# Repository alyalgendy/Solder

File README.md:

# 3-Bit Binary counter

## Schematic Design

## BCP Design
### Front

### Back

## 3D view

## Features

- Counts from 0 (000) to 7 (111) in binary, covering all 3-bit combinations.
- Three LEDs display the binary output, each representing one bit.
- Easily observe the counter state through the LED indicators.
- Optimized for a small, easy-to-assemble printed circuit board.
- Ideal for learning and demonstrating binary counting and digital electronics basics.
- Uses standard logic Transistors and LEDs for efficient operation.

## BOM
- 2  Battery holder
- 1  10μF Capacitor
- 3  LEDs
- 9  NPN transistors
- 1  Push Button
- 14 100 Ω Resistor
- 3  220 Ω Resistor
- 6  4.7 kΩ Resistor
- 4  47 kΩ Resistor

Made by `@Aly Al-gendy` on slack :D

Made as a part of http://solder.hackclub.com/!

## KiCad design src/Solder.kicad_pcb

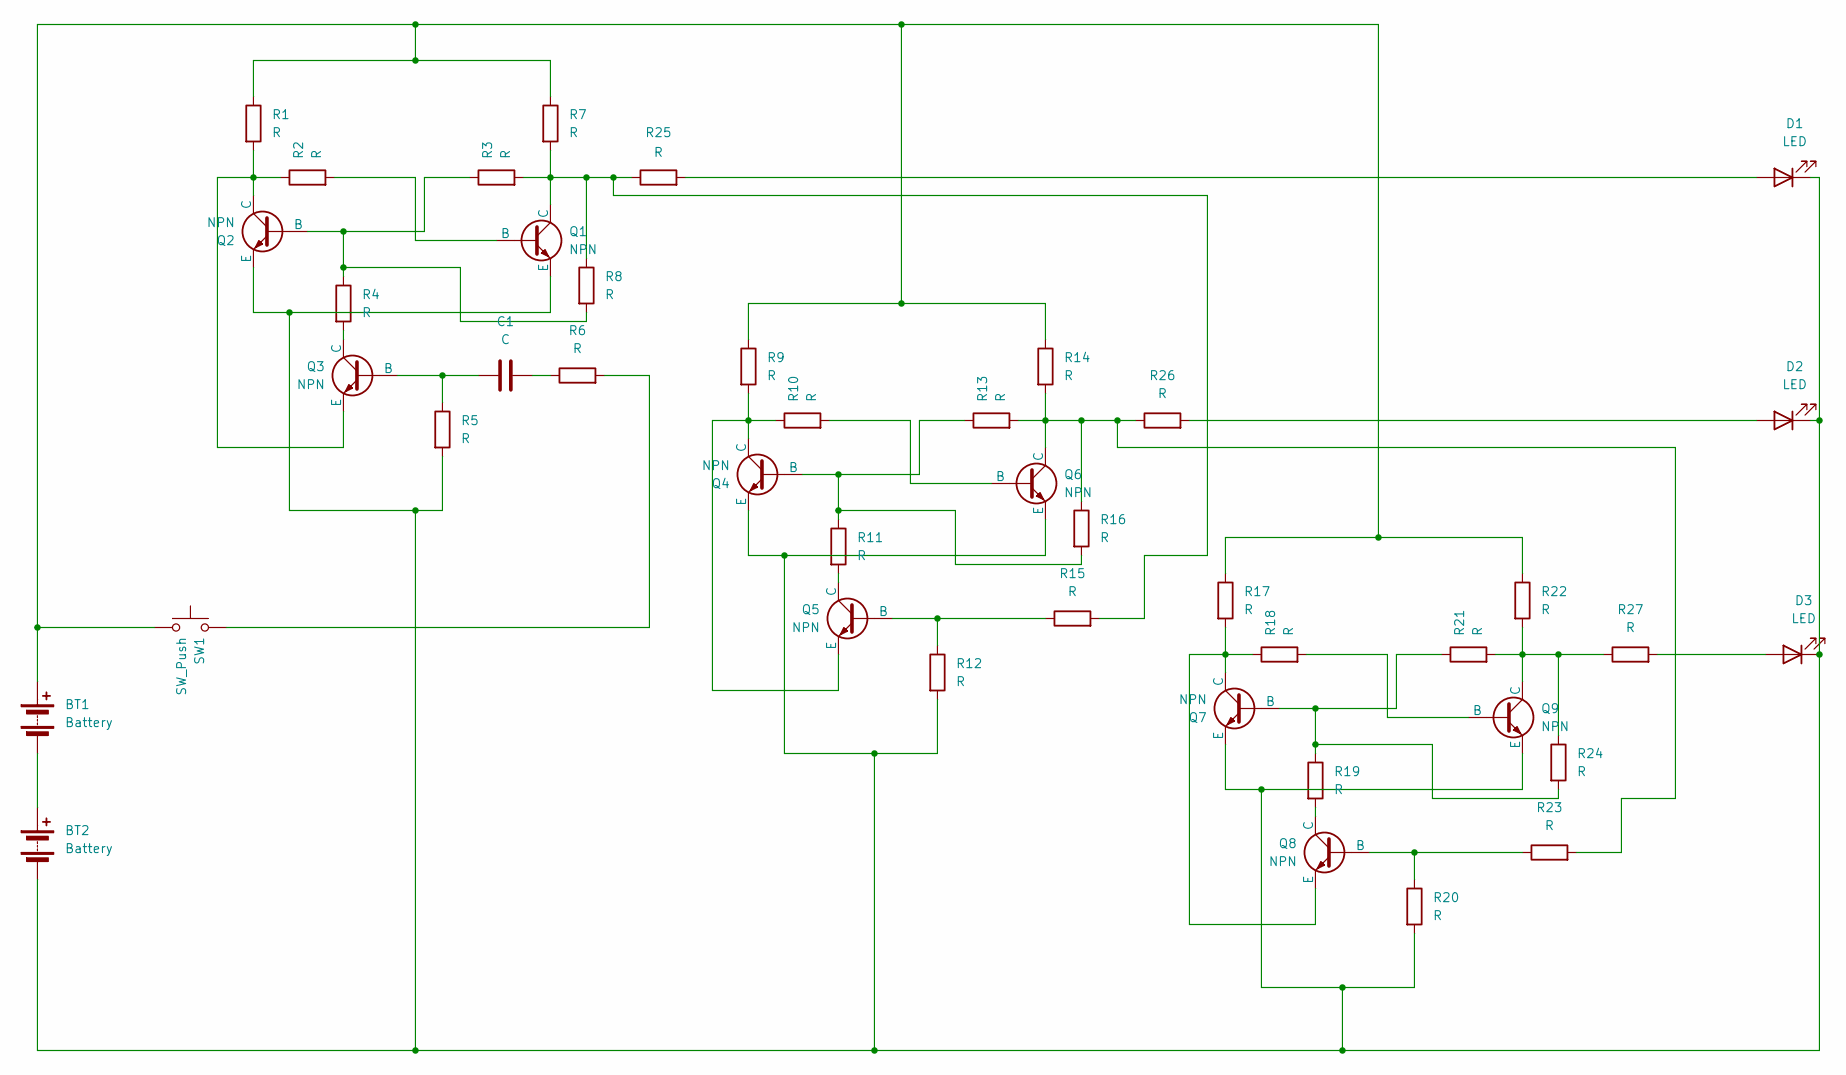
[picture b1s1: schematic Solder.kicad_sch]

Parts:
BT1, BT2: Battery; BatteryHolder_Keystone_3034_1x20mm
C1: C; CP_Radial_D8.0mm_P5.00mm
D1, D2, D3: LED; LED_D5.0mm
Q1, Q2, Q3, Q4, Q5, Q6, Q7, Q8, Q9: NPN; TO-92L_HandSolder
R1, R2, R3, R4, R5, R6, R7, R8, R9, R10, R11, R12, R13, R14, R15, R16, R17, R18, R19, R20, R21, R22, R23, R24, R25, R26, R27: R; R_Axial_DIN0207_L6.3mm_D2.5mm_P7.62mm_Horizontal
SW1: SW_Push; SW_PUSH_6mm

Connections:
unnamed: BT1.1 (+), R1.1, R7.1, R9.1, R14.1, R17.1, R22.1, SW1.1
unnamed: BT1.2 (-), BT2.1 (+)
unnamed: BT2.2 (-), D1.1 (K), D2.1 (K), D3.1 (K), Q1.3 (E), Q2.3 (E), Q4.3 (E), Q6.3 (E), Q7.3 (E), Q9.3 (E), R5.2, R12.2, R20.2
unnamed: C1.2, R6.1
unnamed: D1.2 (A), R25.2
unnamed: D2.2 (A), R26.2
unnamed: D3.2 (A), R27.2
unnamed: Q1.2 (B), R2.2
unnamed: Q1.1 (C), R3.2, R7.2, R8.1, R15.2, R25.1
unnamed: Q2.2 (B), R3.1, R4.1, R8.2
unnamed: Q2.1 (C), Q3.3 (E), R1.2, R2.1
unnamed: C1.1, Q3.2 (B), R5.1
unnamed: Q3.1 (C), R4.2
unnamed: Q4.2 (B), R11.1, R13.1, R16.2
unnamed: Q4.1 (C), Q5.3 (E), R9.2, R10.1
unnamed: Q5.2 (B), R12.1, R15.1
unnamed: Q5.1 (C), R11.2
unnamed: Q6.2 (B), R10.2
unnamed: Q6.1 (C), R13.2, R14.2, R16.1, R23.2, R26.1
unnamed: Q7.2 (B), R19.1, R21.1, R24.2
unnamed: Q7.1 (C), Q8.3 (E), R17.2, R18.1
unnamed: Q8.2 (B), R20.1, R23.1
unnamed: Q8.1 (C), R19.2
unnamed: Q9.2 (B), R18.2
unnamed: Q9.1 (C), R21.2, R22.2, R24.1, R27.1
unnamed: R6.2, SW1.2

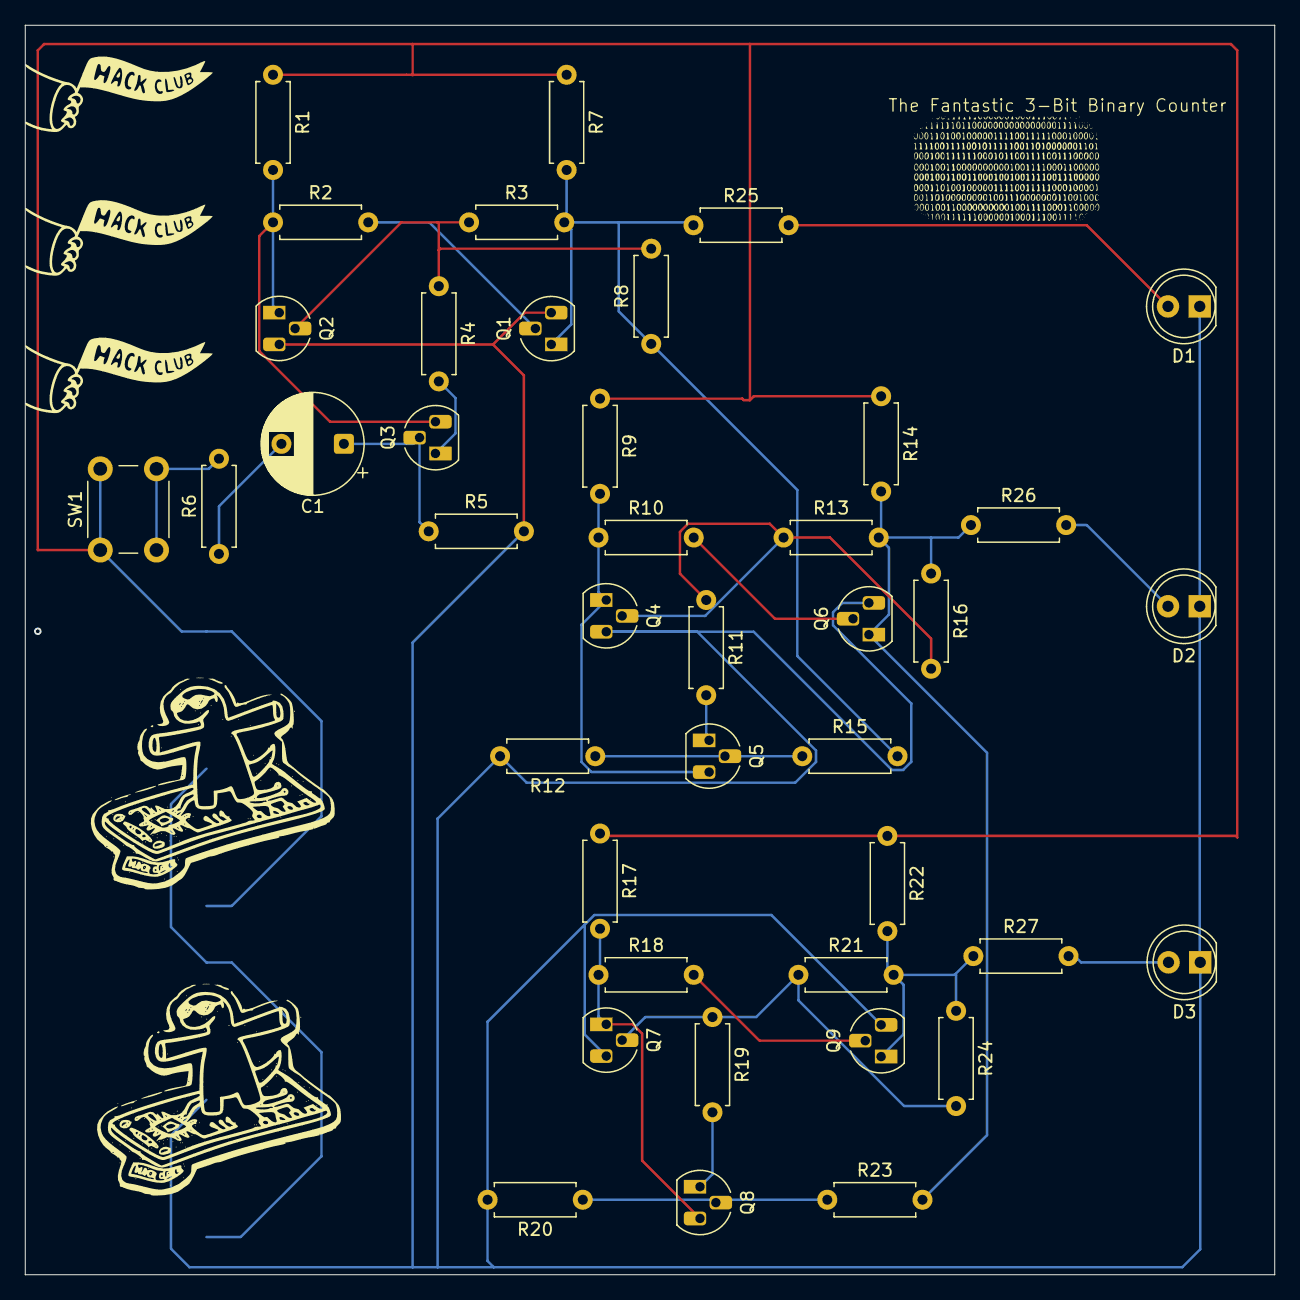
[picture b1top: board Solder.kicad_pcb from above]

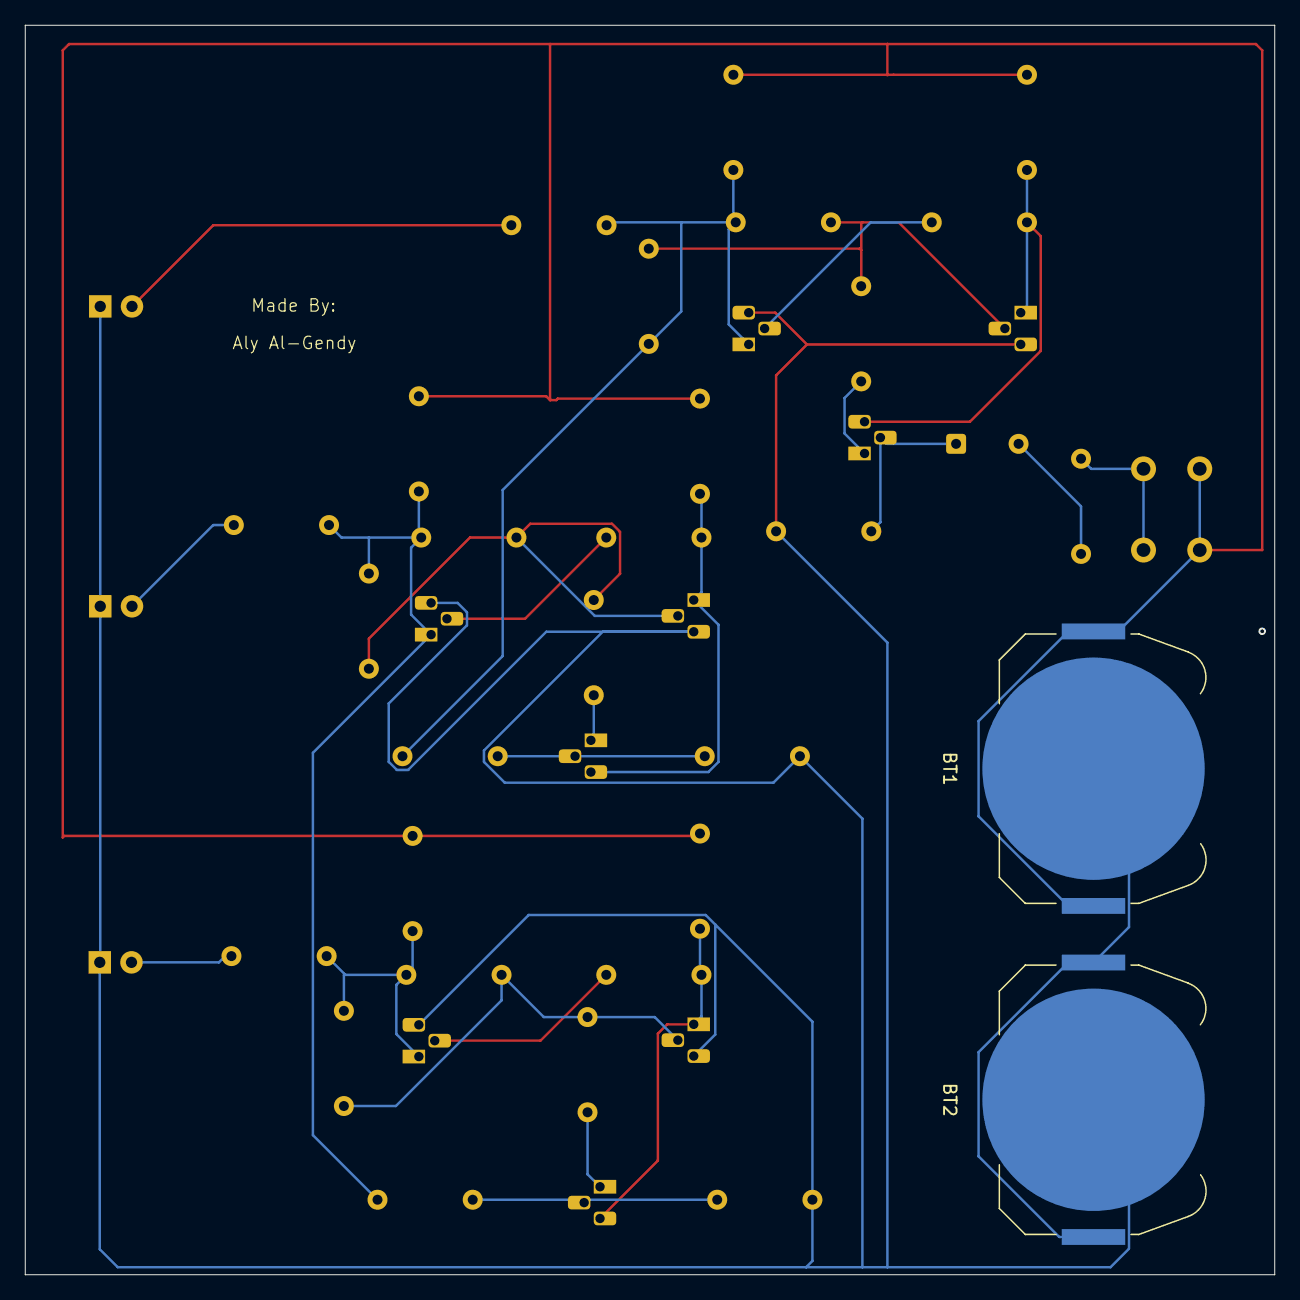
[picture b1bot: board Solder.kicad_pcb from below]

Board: 2 copper layers, 100.0 x 100.0 mm, 43 parts (2 on the bottom side), 26 nets.
